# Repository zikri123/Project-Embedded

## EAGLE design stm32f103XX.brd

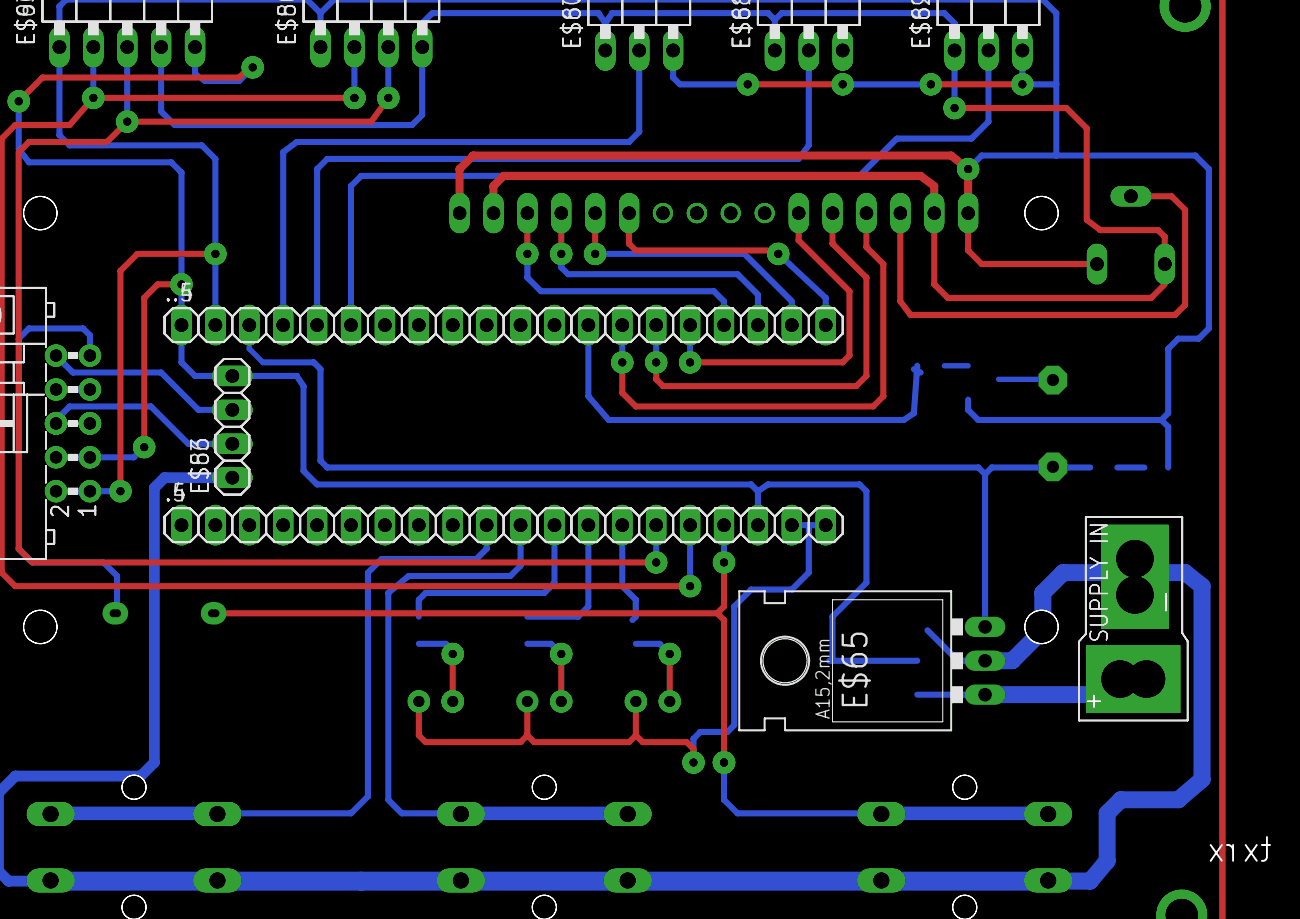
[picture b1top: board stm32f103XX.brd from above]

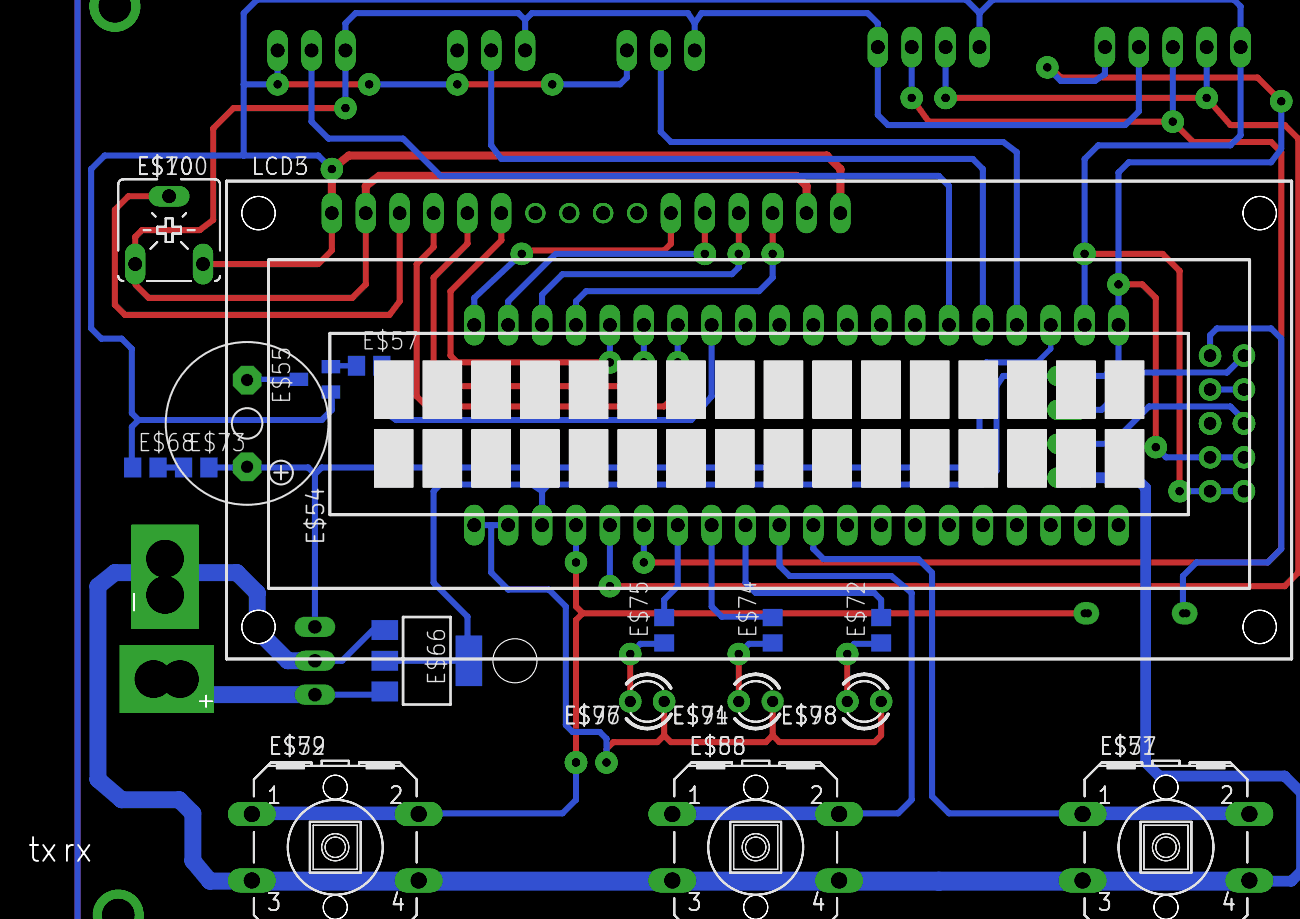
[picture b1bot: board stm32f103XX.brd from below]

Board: 2 copper layers, 46 parts (25 on the bottom side), 9 nets.

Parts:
.4, .5, ..4, ..5: 1X20
E$51, E$52, E$58, E$77, E$79, E$85: B3F-40XX
E$53, E$80: ML10L
E$54: F/QMX
E$55: SC59-EBC
E$56, E$83: 1X04
E$57, E$68, E$72, E$73, E$74, E$75: R0805
E$59, E$86: 1X04/90
E$60, E$61, E$62, E$87, E$88, E$89: 1X03/90
E$63, E$90: 1X05/90
E$65: 78XXL
E$66: SOT223
E$69, E$102: SUP
E$70, E$100: CA6V
E$71, E$76, E$78, E$94, E$97, E$98: LED3MM
LCD3, LCD5: TUXGR_16X2_R2

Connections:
S$4: ..5.1, ..5.2, ..5.3, E$83.1, E$83.2, E$83.3, E$83.4
S$6: E$80.3, E$80.5
S$43: .4.15, .4.16, .4.17, .4.18, .4.19, .4.20, ..4.1, ..4.2, ..4.3, ..4.7, ..4.8, ..4.9, ..4.14, ..4.15, ..4.16, ..4.17, ..4.18, E$53.2, E$53.3, E$53.4, E$53.5, E$53.6, E$53.9, E$53.10, E$56.1, E$56.2, E$56.3, E$56.4, E$59.1, E$59.2, E$59.3, E$63.1, E$63.2, E$63.3, E$63.5, E$65.GND, E$65.OUT, E$70.A, E$70.E, E$71.A, E$76.A, E$78.A
S$146: ..4.4, ..4.5, ..4.6, E$60.2, E$61.2, E$62.2
S$147: E$53.7, E$53.8
S$154: ..5.4, ..5.5, ..5.6, E$87.2, E$88.2, E$89.2
S$161: E$59.4, E$60.1, E$61.1, E$62.1, E$63.4
S$174: E$86.4, E$87.1, E$88.1, E$89.1, E$90.4
S$179: .5.10, .5.15, .5.16, .5.17, .5.18, .5.19, .5.20, ..5.7, ..5.8, ..5.9, ..5.14, ..5.15, ..5.16, ..5.17, ..5.18, E$80.2, E$80.4, E$80.6, E$80.9, E$80.10, E$86.1, E$86.2, E$86.3, E$90.1, E$90.2, E$90.3, E$90.5, E$94.A, E$97.A, E$98.A, E$100.A, E$100.E
